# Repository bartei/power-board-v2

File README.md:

# Raspberry Power Board

This simple power board is used in conjunction with the rotary-controller board. It provides a reliable power source for the Raspberry Pi and additionally it includes an RS485 interface
chip which allows easy communication with any external RS485 device.

The UART to RS485 converter chip is powered by the 3.3v generated by the Raspberry.
A few convenient LEDs provide some status information about the power supplies and the communication activity detected on the RS485 TX line coming from the SBC.

When powering up the board without an SBC connected to it, only the 5V status LED will power up.

This power board should be able to provide enough power for the SBC, a display, and a few external devices.

The board can be powered with an AC/DC power supply, making it easy to use with an old school transformer (24VAC max recommended) or any DC power supply (10-36V recommended).

Efficiency and absolute maximum ratins will vary depending on the provided power supply voltage, the selected coil is most efficient when working around 12-18 volts.

When powering the board with a DC power supply, polarity is not relevant, making it harder to make mistakes.

Some basic circuit protection is provided by means of ESD diodes and a resettable fuse.

The selected SR485 interface chip is compatible with 3V3 signals (same as the SBC) and it includes ESD protection, making it a simple choice for interfacing with external devices without
many extra components.

When connecting the serial line with long distance wires make sure to properly select a termination resistor in your line and ensure also that proper biasing resistors are placed 
in order to maximize compatibility with 3rd party serial devices. 330 Ohm resistors are commonly used for line biasing, whereas 120 Ohm are generally used for line termination.

Propoer component selection, especially when dealing with long distances, together with suitable cable selection, are critical for a reliable and fast connection between your devices.

The project includes also suitable production files that are currently being used for manufacturing, if you see mistakes or have ideas that you want to suggest for this project, shoot
me an email: bartei81@gmail.com.

Thanks for your interest in the project!

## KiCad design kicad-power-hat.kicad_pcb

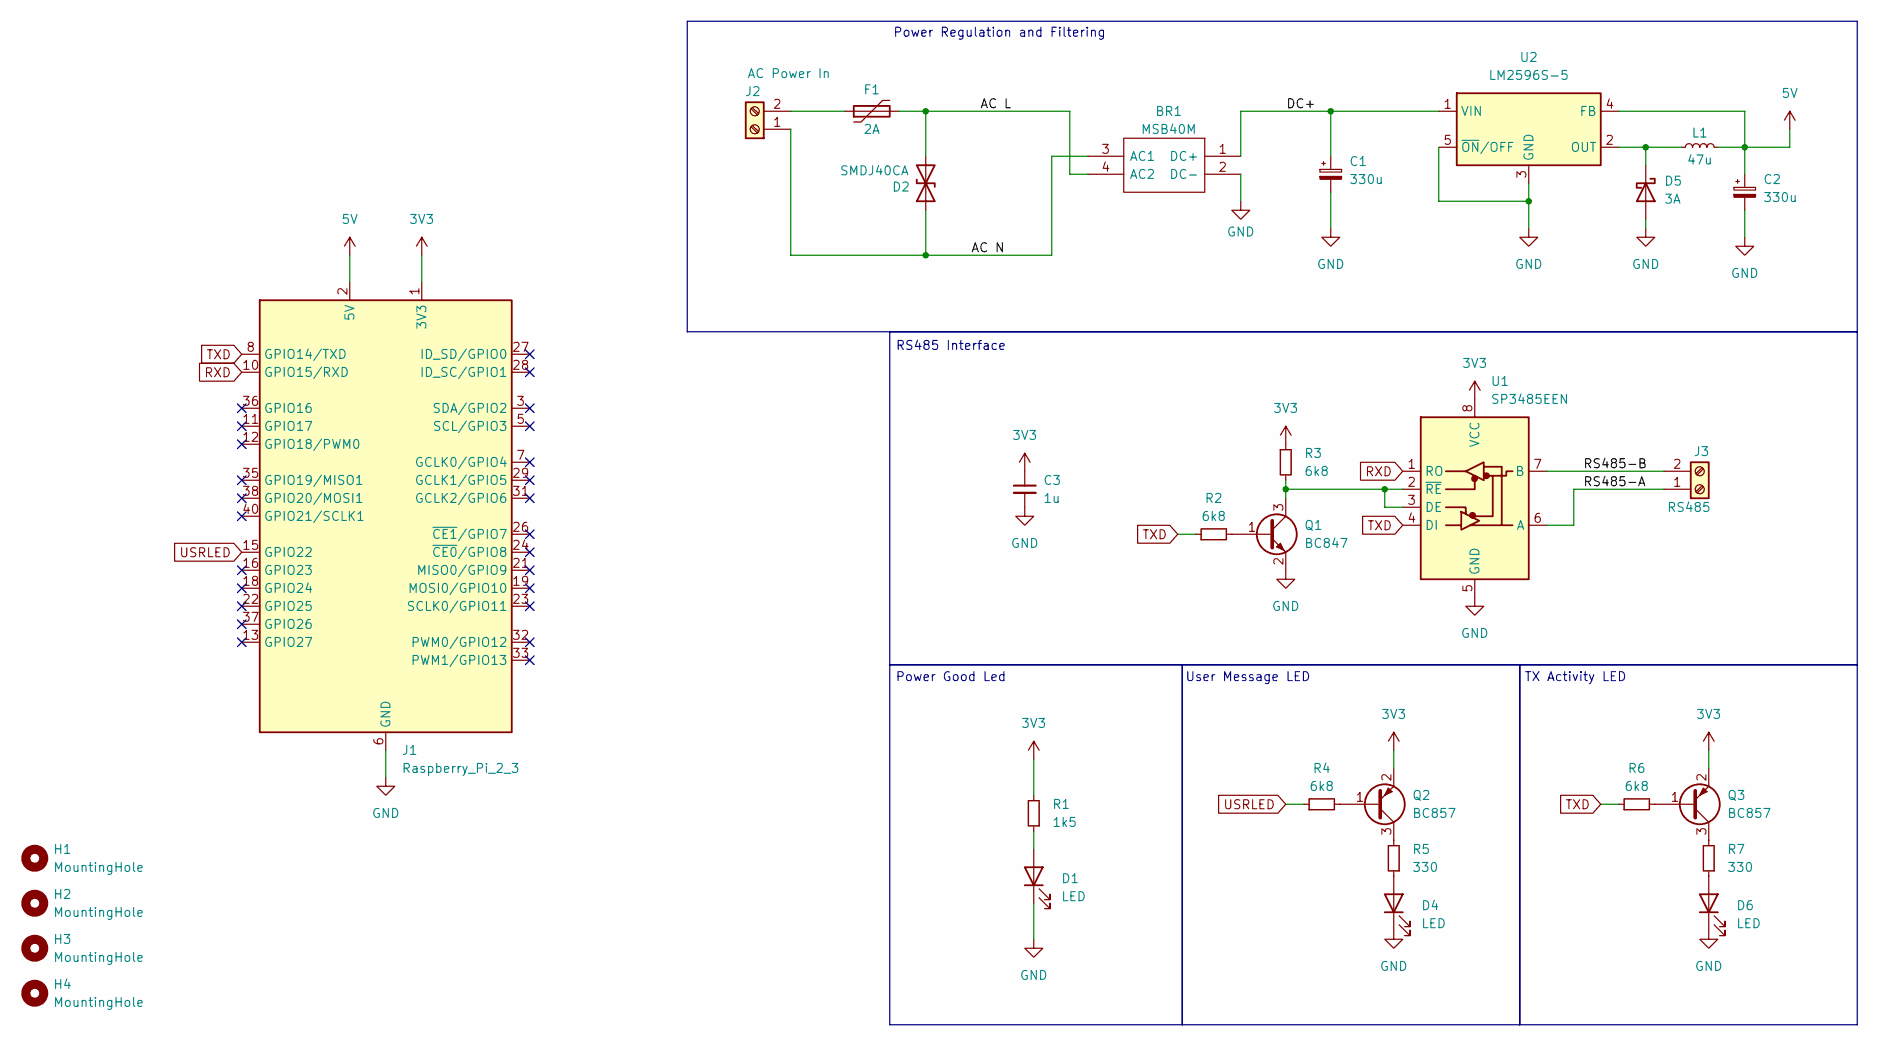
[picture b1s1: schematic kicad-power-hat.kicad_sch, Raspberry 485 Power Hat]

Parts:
BR1: MSB40M; SOTFL510P865X150-4N; Manufacturer_Part_Number MSB40M
C1, C2: 330u; CP_Elec_10x12.6; LCSC C128512
C3: 1u; C_0805_2012Metric; LCSC C24123
D1, D4, D6: LED; D_0603_1608Metric; LCSC C965799
D2: SMDJ40CA; D_SMC; LCSC C84730
D5: 3A; D_SMA; LCSC C8678
F1: 2A; Fuse_1812_4532Metric; LCSC C960026
H1, H2, H3, H4: MountingHole; MountingHole_2.7mm_M2.5
J1: Raspberry_Pi_2_3; PinHeader_2x20_P2.54mm_Vertical
J2: AC Power In; TerminalBlock_Phoenix_MKDS-1,5-2-5.08_1x02_P5.08mm_Horizont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
J3: RS485; TerminalBlock_Phoenix_MKDS-1,5-2-5.08_1x02_P5.08mm_Horizont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
L1: 47u; L_Sunlord_SWRB1207S; LCSC C2929503
Q1: BC847; SOT-23; LCSC C181140
Q2, Q3: BC857; SOT-23; LCSC C8666
R1: 1k5; R_0805_2012Metric; LCSC C4310
R2, R3, R4, R6: 6k8; R_0805_2012Metric; LCSC C17772
R5, R7: 330; R_0805_2012Metric; LCSC C17630
U1: SP3485EEN; SOP-8_3.9x4.9mm_P1.27mm; LCSC C668205
U2: LM2596S-5; TO-263-5_TabPin3; LCSC C347421

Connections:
3V3: C3.1, J1.1 (3V3), J1.17 (3V3), Q2.2 (E), Q3.2 (E), R1.2, R3.1, U1.8 (VCC)
5V: C2.1, J1.2 (5V), J1.4 (5V), L1.2, U2.4 (FB)
/AC L: BR1.4 (AC2), D2.2 (A2), F1.2
/AC N: BR1.3 (AC1), D2.1 (A1), J2.1
/DC+: BR1.1 (DC+), C1.1, U2.1 (VIN)
/RS485-A: J3.1, U1.6 (A)
/RS485-B: J3.2, U1.7 (B)
GND: BR1.2 (DC-), C1.2, C2.2, C3.2, D1.1 (K), D4.1 (K), D5.2 (A), D6.1 (K), J1.6 (GND), J1.9 (GND), J1.14 (GND), J1.20 (GND), J1.25 (GND), J1.30 (GND), J1.34 (GND), J1.39 (GND), Q1.2 (E), U1.5 (GND), U2.3 (GND), U2.5 (~ON/OFF)
unnamed: D1.2 (A), R1.1
unnamed: D4.2 (A), R5.1
unnamed: D5.1 (K), L1.1, U2.2 (OUT)
unnamed: D6.2 (A), R7.1
unnamed: F1.1, J2.2
unnamed: Q1.1 (B), R2.2
unnamed: Q1.3 (C), R3.2, U1.2 (~RE), U1.3 (DE)
unnamed: Q2.1 (B), R4.2
unnamed: Q2.3 (C), R5.2
unnamed: Q3.1 (B), R6.2
unnamed: Q3.3 (C), R7.2
RXD: J1.10 (GPIO15/RXD), U1.1 (RO)
TXD: J1.8 (GPIO14/TXD), R2.1, R6.1, U1.4 (DI)
USRLED: J1.15 (GPIO22), R4.1

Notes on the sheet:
Power Regulation and Filtering
Power Good Led
TX Activity LED
RS485 Interface
User Message LED

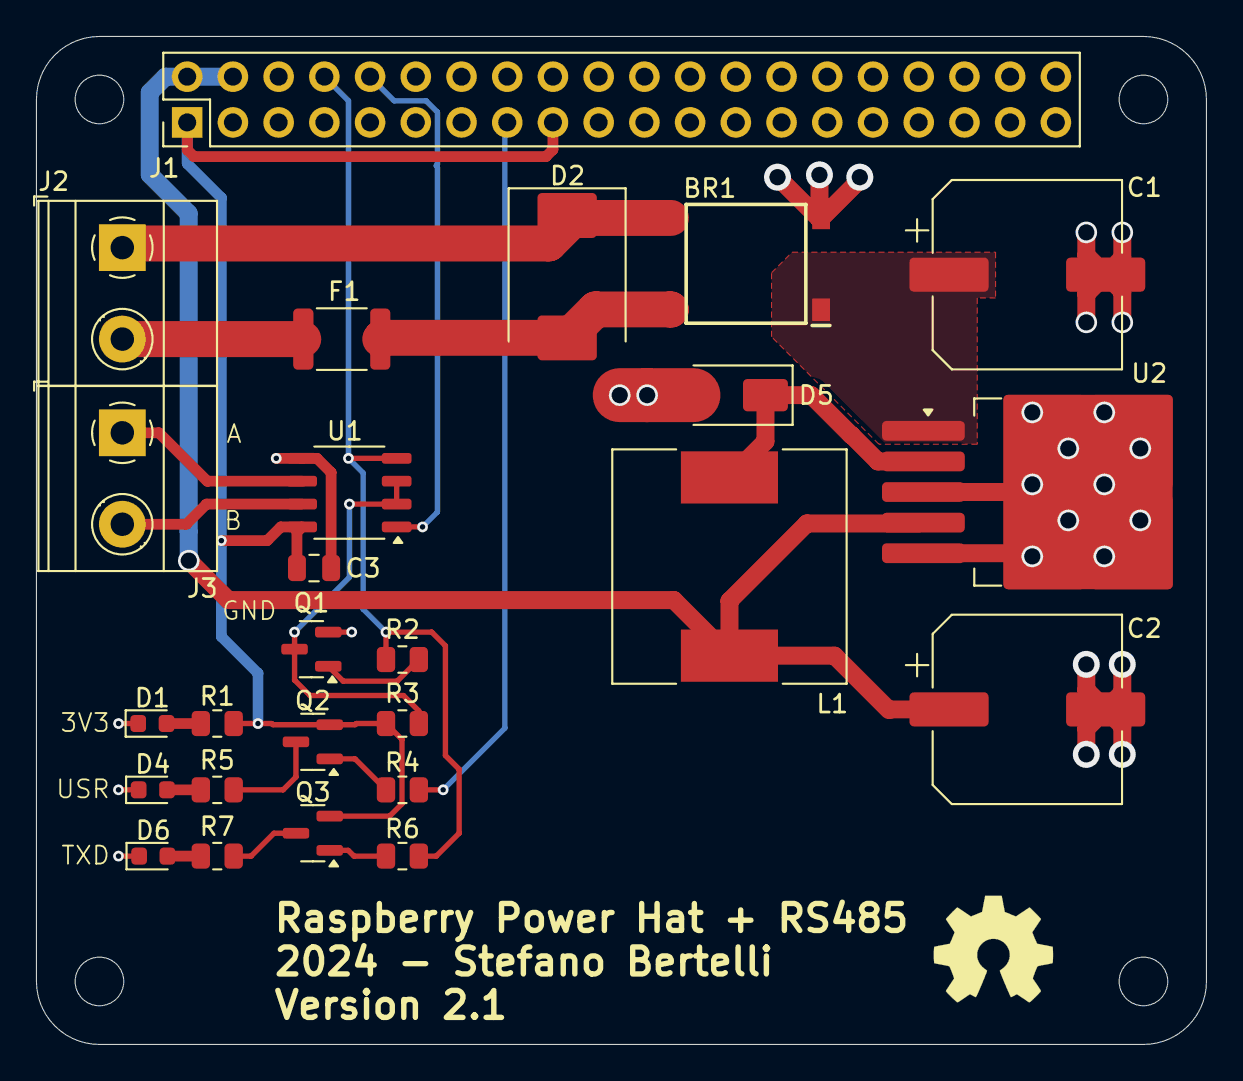
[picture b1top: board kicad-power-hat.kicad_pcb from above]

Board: 2 copper layers, 65.0 x 56.0 mm, 30 parts (0 on the bottom side), 22 nets.

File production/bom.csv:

Designator,Footprint,Quantity,Value,LCSC Part #
BR1,SOTFL510P865X150-4N,1,MSB40M,
"C1, C2",CP_Elec_10x12.6,2,330u,C128512
C3,0805,1,1u,C24123
"D1, D4, D6",0603,3,LED,C965799
D2,D_SMC,1,SMDJ40CA,C84730
D5,D_SMA,1,3A,C8678
F1,1812,1,2A,C960026
"H1, H2, H3, H4",MountingHole_2.7mm_M2.5,4,MountingHole,
J1,PinHeader_2x20_P2.54mm_Vertical,1,Raspberry_Pi_2_3,
J2,"TerminalBlock_Phoenix_MKDS-1,5-2-5.08_1x02_P5.08mm_Horizontal",1,AC Power In,
J3,"TerminalBlock_Phoenix_MKDS-1,5-2-5.08_1x02_P5.08mm_Horizontal",1,RS485,
L1,L_Sunlord_SWRB1207S,1,47u,C2929503
Q1,SOT-23,1,BC847,C181140
"Q2, Q3",SOT-23,2,BC857,C8666
R1,0805,1,1k5,C4310
"R2, R3, R4, R6",0805,4,6k8,C17772
"R5, R7",0805,2,330,C17630
U1,SOP-8_3.9x4.9mm_P1.27mm,1,SP3485EEN,C668205
U2,TO-263-5_TabPin3,1,LM2596S-5,C347421

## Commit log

2024-03-03 wip: update to layout and labels
2024-03-07 Remove output files from root folder
2024-03-07 Updated pcb
2024-03-08 fix: cleanup backups and update crowbar diode part number
2024-04-17 fix: Update holes pattern and footprint for rectifier
